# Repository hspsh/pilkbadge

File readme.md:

# PILKBADGE

Buranyaaa! If you love ironically drinking pilk (50% pepsi, 50% milk mix), or like anime women, this badge is for you!

This is a fun project we did at hackerspace. @weaselcore did the art, @critbit made it into a PCB.

After inserting the bottles, the eyes glow up. Inserting bottles requires a bit of wiggling, since the holes are a bit skewed - after inserting, they more-or-less stay in place.

## how to assemble your badge

You will need:
* 1x Pilkbadge neko
* 1x milk bottle, 1x bepis bottle
* 2x LEDs, size `0603` or `0805` (soldered upside-down)
* 2x `0603` resistors, value between 470 and 200 ohm (the brightest)
* 2x 4pin 2.54mm headers (soldered to the bottles)
* a generic CR2032 battery holder
* a glued-in pin (optional)

On 1st revision board, there's also an option for using a LiPo charger PCB instead of CR2032 holder, but this is not supported, nor advised. Do it on your own risk.

## Images

## Credits
* Random person from CCC, whose name I will never know, but they noticed an error in previous readme. They also liked being called random person, I think. You can always open an issue, random person, to become a non-random one. Thanks!
* Another random person who suggested that Neko Arc could also hold other items than pilk ingridients - we might add this feature in future revisions.
* Non-random @andigandi for design tips and motivating us to deal with licensing the project.

## Licensing Information
The hardware design files, including schematics and PCB layout (excluding silkscreen artwork and outline design), are licensed under the CERN Open Hardware Licence v2 [CERN-OHL-W](https://ohwr.org/project/cernohl/-/wikis/uploads/f773df342791cc55b35ac4f907c78602/cern_ohl_w_v2.pdf).

Artwork and outline design © 2023 by [Ewa Kielska](https://www.behance.net/dziaberlia55f5) are licensed under [CC BY-NC-ND 4.0](https://creativecommons.org/licenses/by-nc-nd/4.0/)

All documentation is released under [CC BY-SA 4.0](https://creativecommons.org/licenses/by-sa/4.0/)

In summary, you are free to use schematic and general concept of this project according to `CERN-OHL-W` license. If you want to include the artwork, you must adhere to `CC BY-NC-ND 4.0` too.

We are open to either adjust these licensing terms, or providing the design files with alternative licensing terms in special cases. Feel free to open issue then.

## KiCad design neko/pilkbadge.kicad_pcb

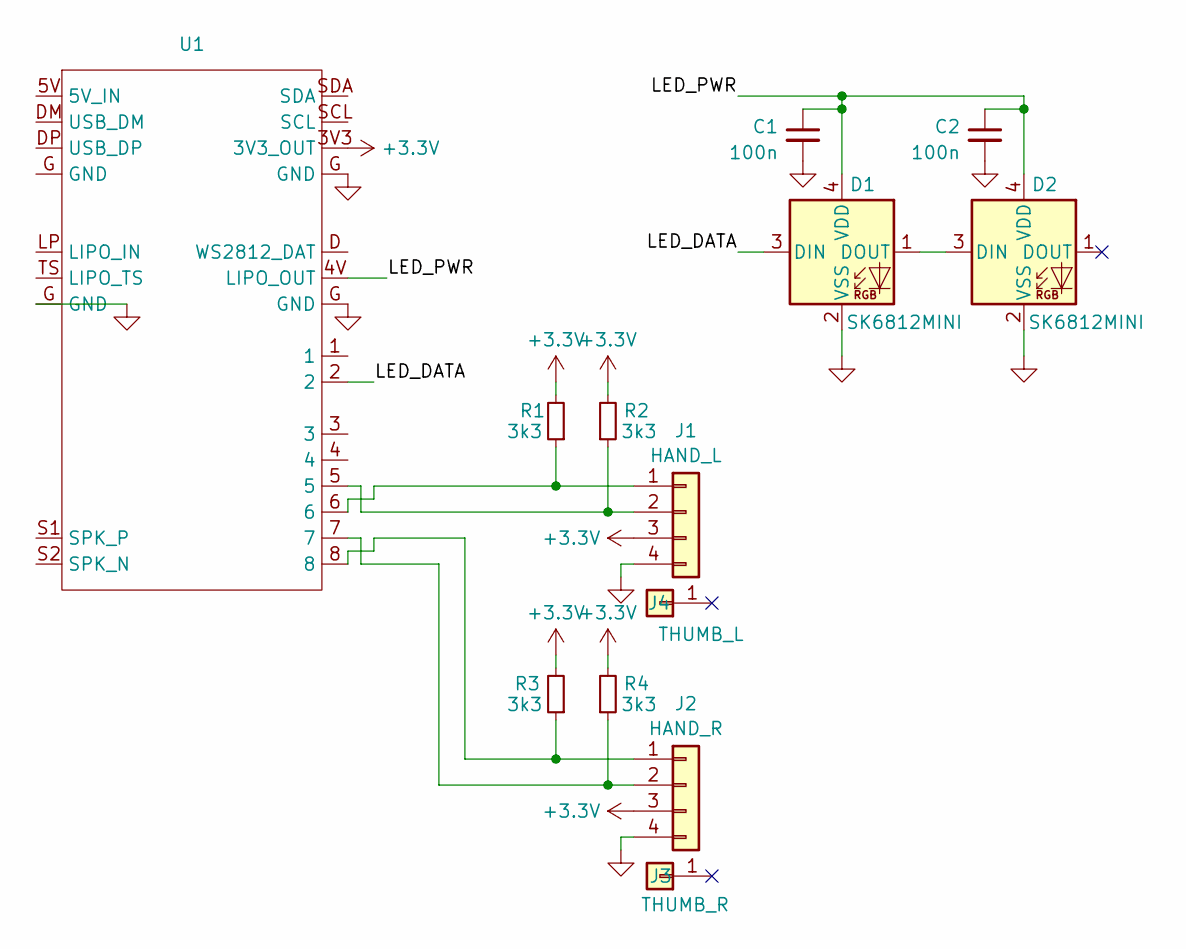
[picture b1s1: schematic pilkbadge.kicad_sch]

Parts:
C1, C2: 100n; C_0603_1608Metric_Pad1.08x0.95mm_HandSolder
D1, D2: SK6812MINI; SK6812MINI_PLCC4_UPSIDEDOWN
J1: HAND_L; Neko_hands
J2: HAND_R; Neko_hands
J3: THUMB_R; PinHeader_1x01_P2.54mm_Vertical
J4: THUMB_L; PinHeader_1x01_P2.54mm_Vertical
R1, R2, R3, R4: 3k3; R_0603_1608Metric_Pad0.98x0.95mm_HandSolder
U1: pilkbrain2

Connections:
+3.3V: J1.3, J2.3, R1.2, R2.2, R3.2, R4.2, U1.3V3 (3V3_OUT)
/LED_DATA: D1.3 (DIN), U1.2
/LED_PWR: C1.1, C2.1, D1.4 (VDD), D2.4 (VDD), U1.4V (LIPO_OUT)
GND: C1.2, C2.2, D1.2 (VSS), D2.2 (VSS), J1.4, J2.4, U1.G (GND)
unnamed: D1.1 (DOUT), D2.3 (DIN)
unnamed: J1.1, R1.1, U1.6
unnamed: J1.2, R2.1, U1.5
unnamed: J2.1, R3.1, U1.8
unnamed: J2.2, R4.1, U1.7

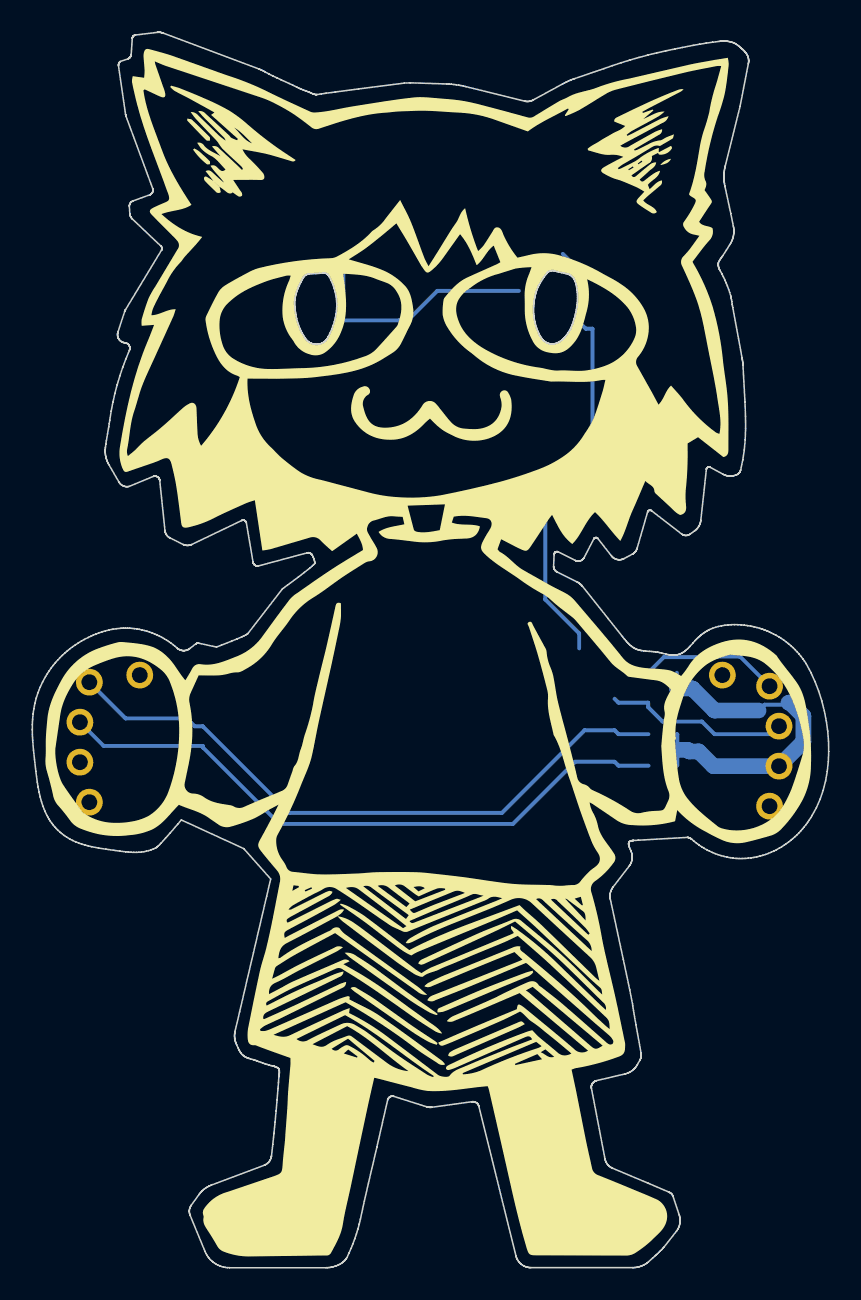
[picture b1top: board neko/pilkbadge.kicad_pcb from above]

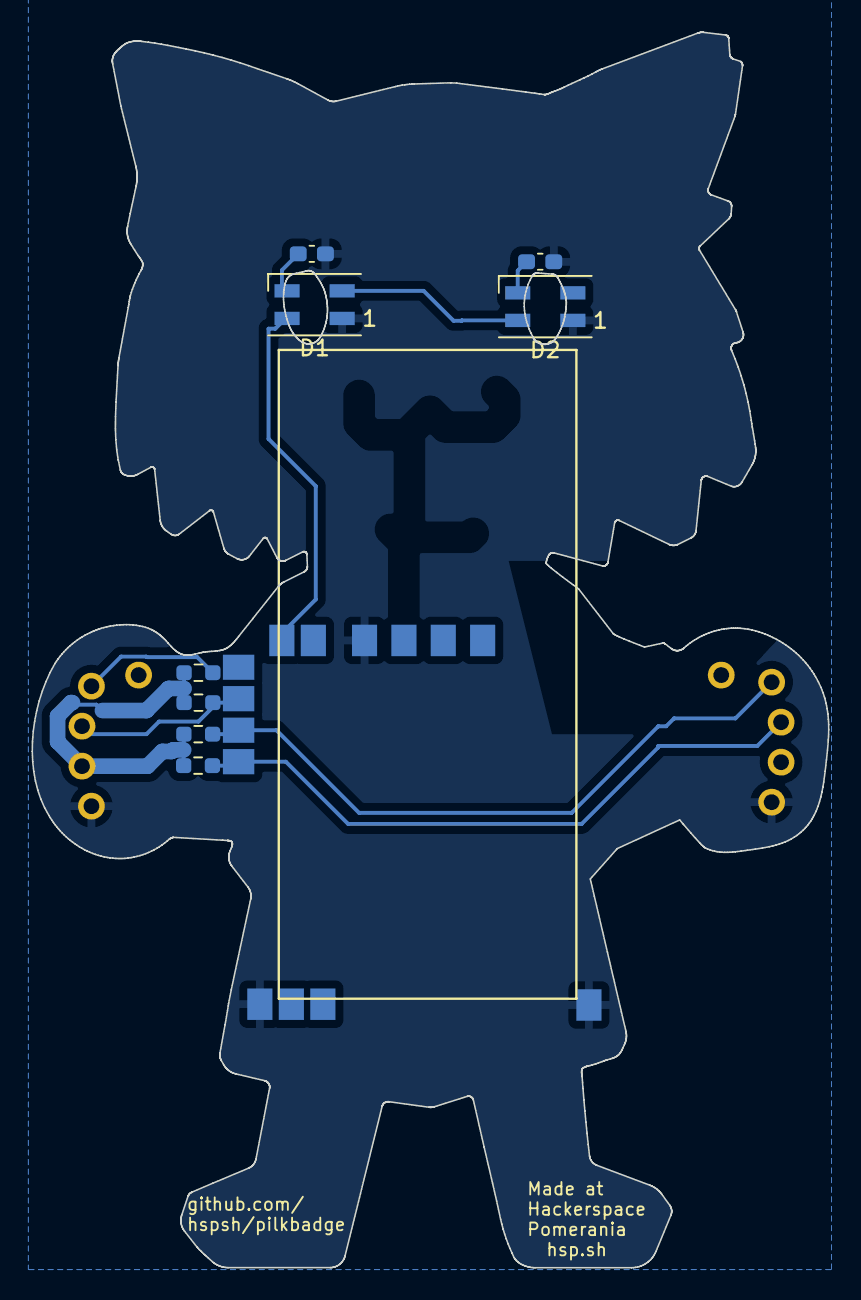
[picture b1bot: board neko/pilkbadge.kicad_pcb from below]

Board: 2 copper layers, 50.6 x 78.5 mm, 13 parts (12 on the bottom side), 9 nets.

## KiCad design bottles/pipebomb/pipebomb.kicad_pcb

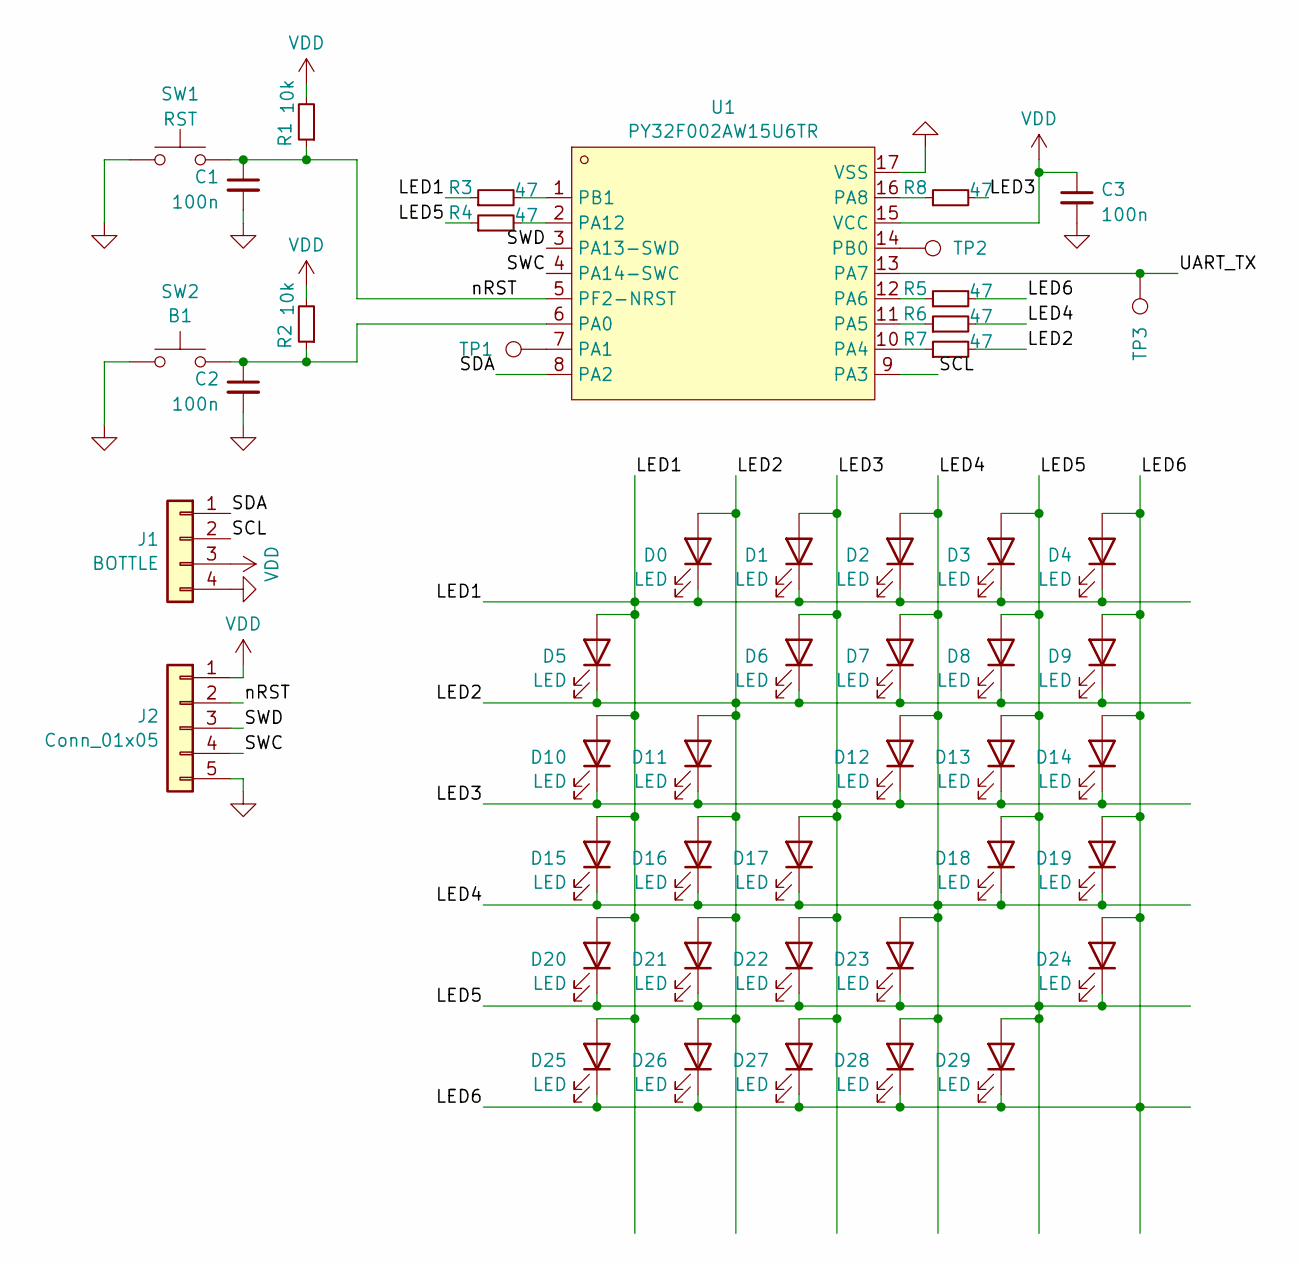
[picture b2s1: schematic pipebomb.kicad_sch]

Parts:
C1, C2, C3: 100n; C_0402_1005Metric; LCSC C1525
D0, D1, D2, D3, D4, D5, D6, D7, D8, D9, D10, D11, D12, D13, D14, D15, D16, D17, D18, D19, D20, D21, D22, D23, D24, D25, D26, D27, D28, D29: LED; LED_0402_1005Metric; LCSC C434445
J1: BOTTLE; PinHeader_1x04_P2.54mm_Vertical; LCSC DNP
J2: Conn_01x05; PinHeader_1x05_P1.27mm_Vertical; LCSC DNP
R1, R2: 10k; R_0402_1005Metric; LCSC C25744
R3, R4, R5, R6, R7, R8: 47; R_0603_1608Metric; LCSC C23182
SW1: RST; SW_SPST_FSMSM; LCSC DNP
SW2: B1; SW_SPST_FSMSM; LCSC DNP
TP1, TP2, TP3: IOPAD; TestPoint_Pad_D1.0mm; LCSC DNP
U1: PY32F002AW15U6TR; TQFN-16_L3.0-W3.0-P0.50-BL-EP1.7; LCSC Part C5291740

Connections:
/LED1: D0.1 (K), D1.1 (K), D2.1 (K), D3.1 (K), D4.1 (K), D5.2 (A), D10.2 (A), D15.2 (A), D20.2 (A), D25.2 (A), R3.1
/LED2: D0.2 (A), D5.1 (K), D6.1 (K), D7.1 (K), D8.1 (K), D9.1 (K), D11.2 (A), D16.2 (A), D21.2 (A), D26.2 (A), R7.2
/LED3: D1.2 (A), D6.2 (A), D10.1 (K), D11.1 (K), D12.1 (K), D13.1 (K), D14.1 (K), D17.2 (A), D22.2 (A), D27.2 (A), R8.2
/LED4: D2.2 (A), D7.2 (A), D12.2 (A), D15.1 (K), D16.1 (K), D17.1 (K), D18.1 (K), D19.1 (K), D23.2 (A), D28.2 (A), R6.2
/LED5: D3.2 (A), D8.2 (A), D13.2 (A), D18.2 (A), D20.1 (K), D21.1 (K), D22.1 (K), D23.1 (K), D24.1 (K), D29.2 (A), R4.1
/LED6: D4.2 (A), D9.2 (A), D14.2 (A), D19.2 (A), D24.2 (A), D25.1 (K), D26.1 (K), D27.1 (K), D28.1 (K), D29.1 (K), R5.2
/SCL: J1.2, U1.9 (PA3)
/SDA: J1.1, U1.8 (PA2)
/SWC: J2.4, U1.4 (PA14-SWC)
/SWD: J2.3, U1.3 (PA13-SWD)
/UART_TX: TP3.1, U1.13 (PA7)
/nRST: C1.1, J2.2, R1.1, SW1.2, U1.5 (PF2-NRST)
GND: C1.2, C2.2, C3.2, J1.4, J2.5, SW1.1, SW2.1, U1.17 (VSS)
unnamed: C2.1, R2.1, SW2.2, U1.6 (PA0)
unnamed: TP1.1, U1.7 (PA1)
unnamed: R7.1, U1.10 (PA4)
unnamed: R6.1, U1.11 (PA5)
unnamed: R5.1, U1.12 (PA6)
unnamed: R8.1, U1.16 (PA8)
unnamed: R4.2, U1.2 (PA12)
unnamed: TP2.1, U1.14 (PB0)
unnamed: R3.2, U1.1 (PB1)
VDD: C3.1, J1.3, J2.1, R1.2, R2.2, U1.15 (VCC)

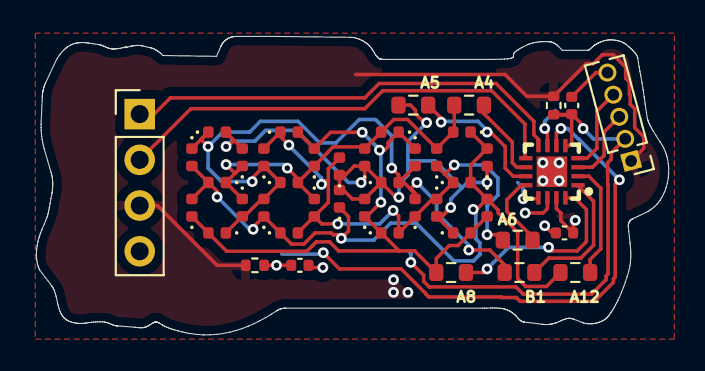
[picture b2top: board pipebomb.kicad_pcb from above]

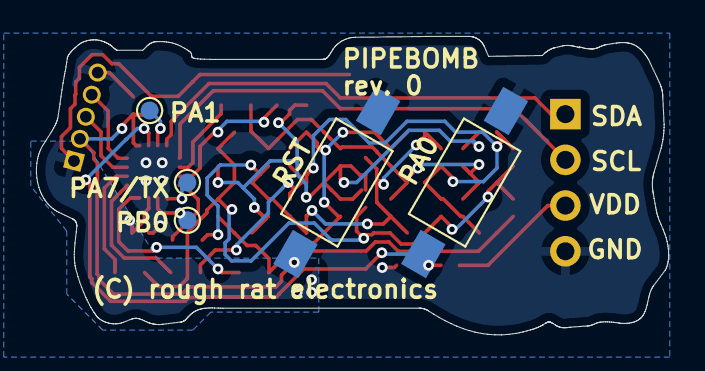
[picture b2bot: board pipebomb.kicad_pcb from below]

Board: 2 copper layers, 35.1 x 16.6 mm, 49 parts (5 on the bottom side), 23 nets.

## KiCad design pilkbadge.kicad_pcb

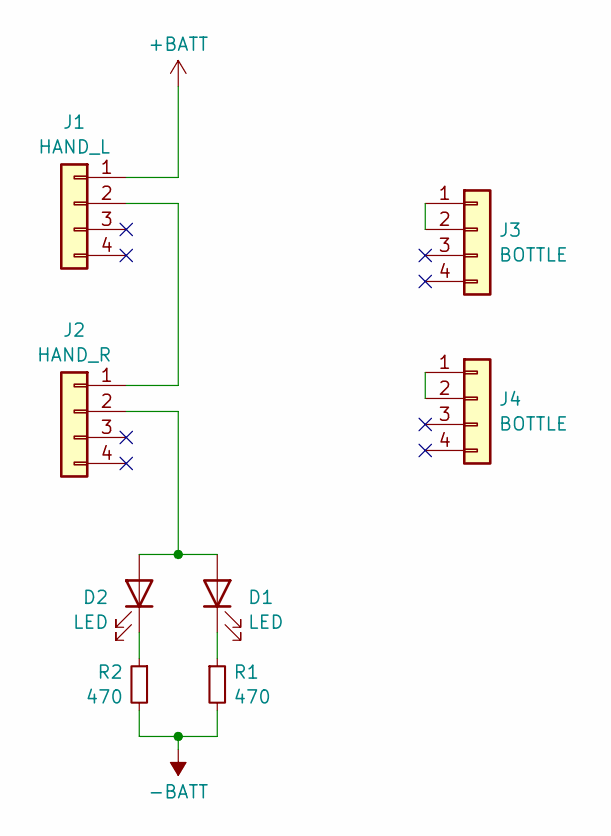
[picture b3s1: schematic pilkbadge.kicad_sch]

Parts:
D1, D2: LED; D_1812_4532Metric_Pad1.30x3.40mm_HandSolder
J1: HAND_L; Neko_hands
J2: HAND_R; Neko_hands
J3, J4: BOTTLE; PinHeader_1x04_P2.54mm_Vertical
R1, R2: 470; LED_0805_2012Metric_Pad1.15x1.40mm_HandSolder

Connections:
+BATT: J1.1
-BATT: R1.2, R2.2
unnamed: D1.2 (A), D2.2 (A), J2.2
unnamed: D1.1 (K), R1.1
unnamed: D2.1 (K), R2.1
unnamed: J1.2, J2.1
unnamed: J3.1, J3.2
unnamed: J4.1, J4.2

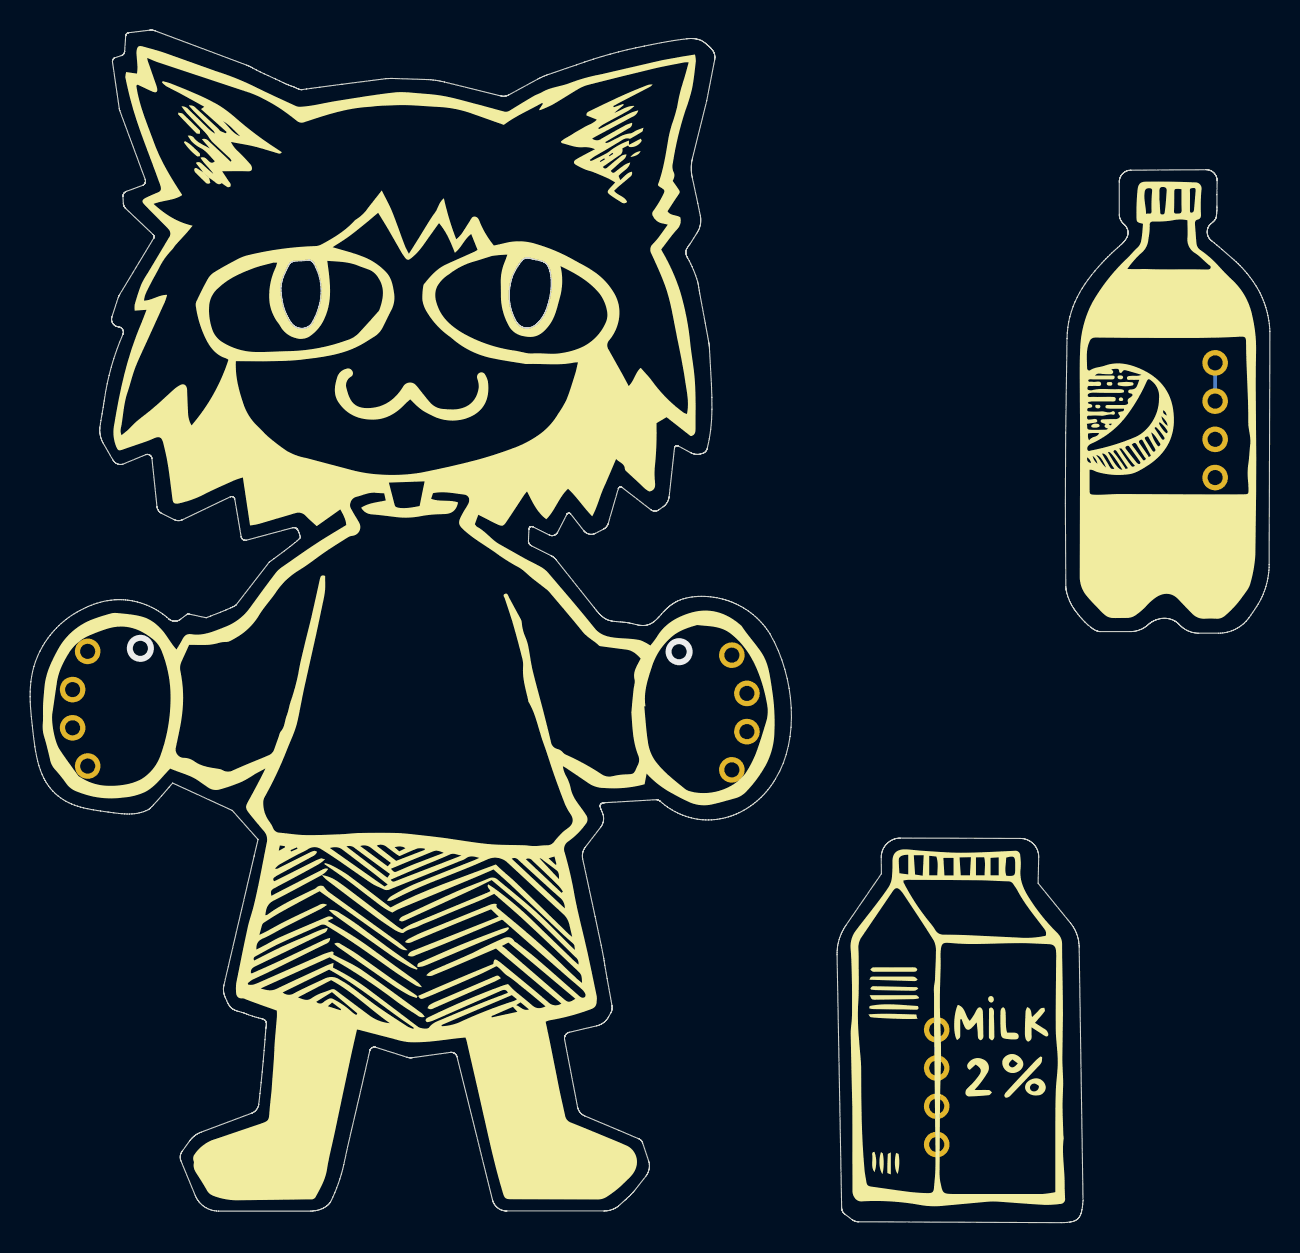
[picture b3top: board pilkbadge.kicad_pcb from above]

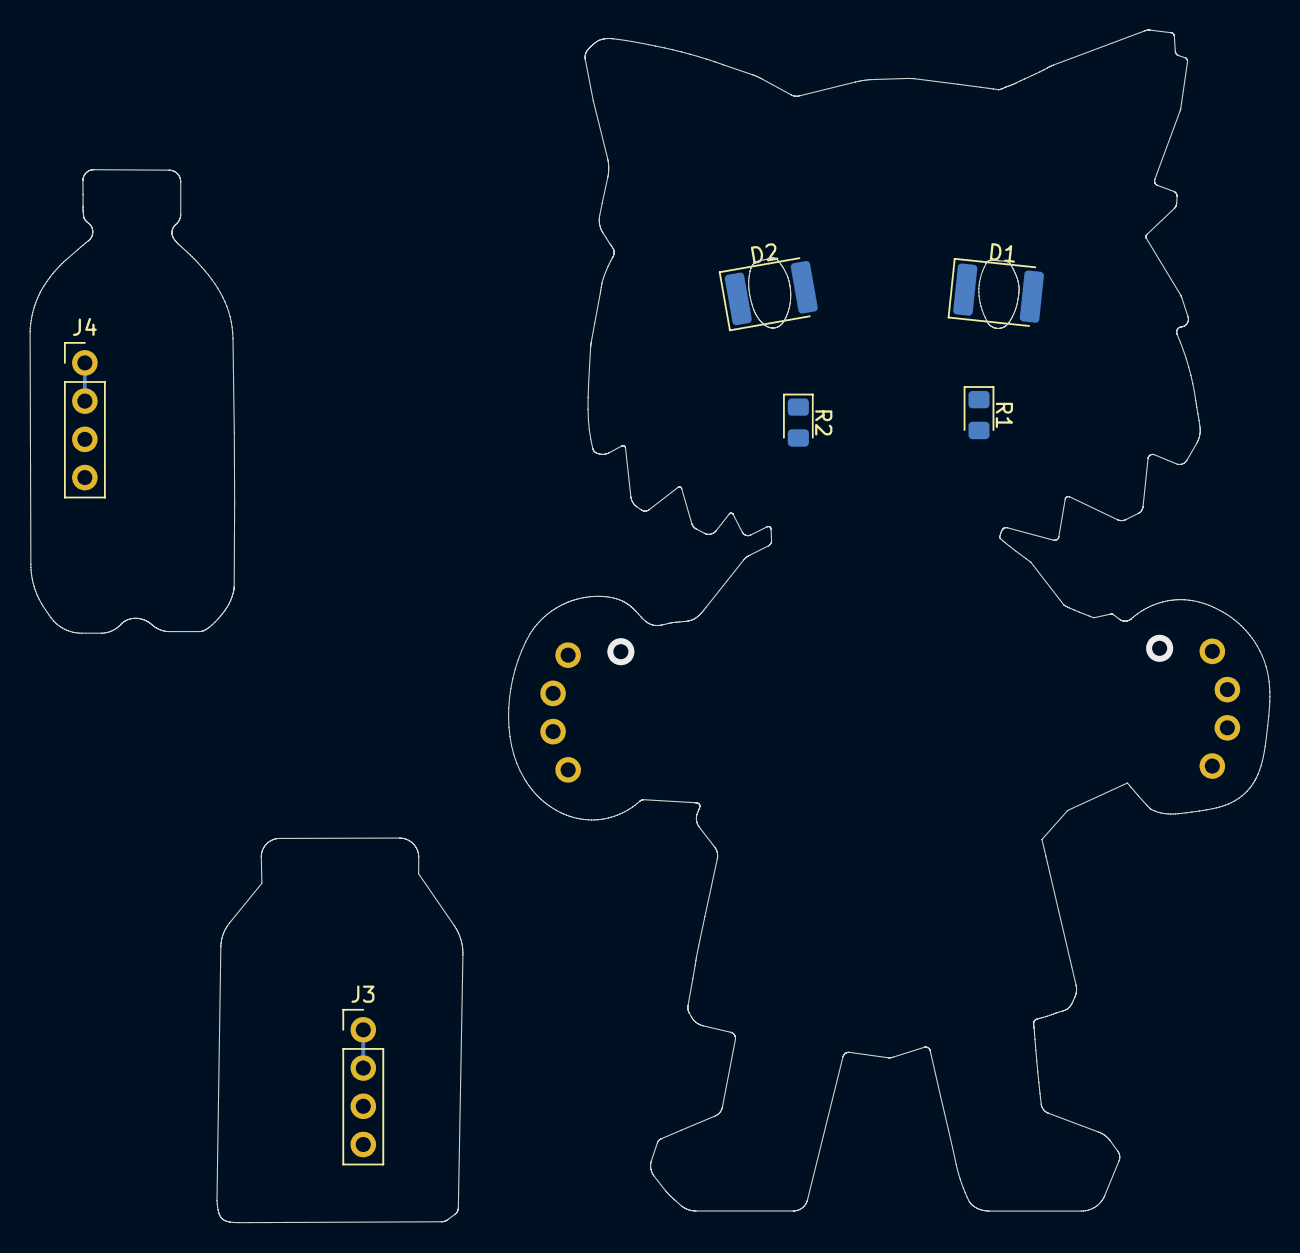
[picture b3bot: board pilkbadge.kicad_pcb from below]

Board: 2 copper layers, 82.4 x 79.2 mm, 8 parts (7 on the bottom side), 7 nets.

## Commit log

2023-11-29 add funny cat
2023-12-01 stuff
2023-12-28 add docs
2023-12-28 AAAAAAAAAAAAAAAAAAAAAAAAAAA
2024-03-30 Add better assembly instructions
2024-03-30 add better render
2024-05-31 add licensing to the project

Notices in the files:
neko/pilkbadge.kicad_pcb:
Artwork © 2023 by Ewa Kielska
licensed under CERN-OHL-W
